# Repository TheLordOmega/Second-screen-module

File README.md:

# Second Screen Module 

A 5" 720x1280 IPS screen expansion module for the Hackxpansion console.

Key features:
* 5" display, 720 x 1280 pixels
* LT7683 display controller
* Arduino-shield-style FFC interface
* Module connector to Hackxpansion console 

## Schematic
![[Pasted image 20261001223714.png]]

## PCB

![[Pasted image 20261001223757.png]]
## 3D Case

![[Pasted image 20261001224142.png]]with 3d case for screen coming when I receive the screen!
## Bill of Materials (excluding console)

Also found in [bom.csv](./bom.csv).

| Item                                            | Price per unit | Nr of units | Total price | Link                                               |
| ----------------------------------------------- | -------------- | ----------- | ----------- | -------------------------------------------------- |
| 5" 720x1280 IPS TFT, LT7683, 4-wire SPI shield  | $50.15         | 1           | $50.15      | https://www.buydisplay.com/                        |
| 2x7 2.54mm pin header (J1)                      | ~$0.20-0.39    | 1           | ~$0.20-0.39 | https://www.aliexpress.com/item/4000186187780.html |
| 1x08 2.54mm pin header (display wire connector) | ~$0.10         | 1           | ~$0.10      | -                                                  |
| MD0/MD1 ID resistors, 0603                      |                | 2           | -           | -                                                  |
| PCB fab                                         |                | 1           | around 10 $ | https://jlcpcb.com/                                |
| **Total**                                       |                |             | ~$60        |                                                    |
## Credits

* Display : [`lt7683` Rust crate](https://docs.rs/lt7683)
* Driver: [`xpanse_api`](https://docs.rs/xpanse-api)
* Display panel: [BuyDisplay ER-TFT050-10](https://www.buydisplay.com/)
* Thanks to Hack Club and the Hackxpansion team for the console platform this module plugs into: https://github.com/hackclub/hackxpansion

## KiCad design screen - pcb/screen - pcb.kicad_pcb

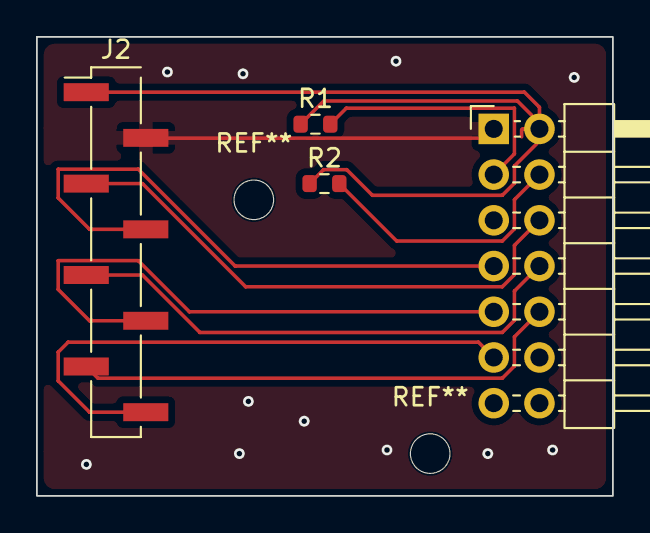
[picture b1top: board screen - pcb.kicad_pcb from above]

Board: 2 copper layers, 32.0 x 25.5 mm, 4 parts (0 on the bottom side), 10 nets.

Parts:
J1: Male_Module
J2: Conn_01x08; PinHeader_1x08_P2.54mm_Vertical_SMD_Pin1Left
R1: 1k; R_0603_1608Metric
R2: 1k3; R_0603_1608Metric

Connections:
+3.3V: J1.2 (3V3), J2.1, R1.1, R2.1
/BL_EN: J1.11 (GPIO6), J2.8
/CS: J1.9 (GPIO4), J2.6
/GND: J1.1 (GND), J2.2
/MISO: J1.8 (GPIO3), J2.5
/MOSI: J1.7 (GPI02), J2.4
/RESET: J1.10 (GPIO5), J2.7
/SCK: J1.6 (GPIO1), J2.3
unnamed: J1.3 (MD0), R1.2
unnamed: J1.4 (MD1), R2.2
